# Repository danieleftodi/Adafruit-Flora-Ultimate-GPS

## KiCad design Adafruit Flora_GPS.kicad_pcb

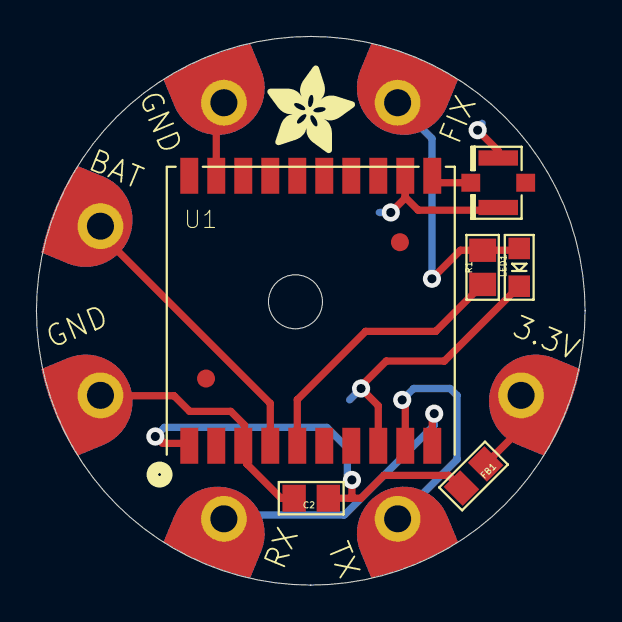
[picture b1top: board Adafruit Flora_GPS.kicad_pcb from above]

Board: 2 copper layers, 30.5 x 30.5 mm, 17 parts (1 on the bottom side), 9 nets.

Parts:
C2: 10uF; 0805
FB1: Ferrite; 0805
FID1, FID2: FIDUCIAL""; FIDUCIAL_1MM
GND0, GND1: SEWTAP-2.0IN; SEWINGTAP_2.0
LED1: FIX; CHIPLED_0805
R1: 1K; 0805
RX0: SEWTAP-2.0IN; SEWINGTAP_2.0
TP1, TP4: SEWTAP-2.0IN; SEWINGTAP_2.0
TX0: SEWTAP-2.0IN; SEWINGTAP_2.0
U1: FGPMMOPA6H
U$6: ADAFRUIT_5MM
U$7: FLORASMALL
U$20: U.FL
UNK3V3IN0: SEWTAP-2.0IN; SEWINGTAP_2.0

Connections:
3.3V: C2.1, FB1.2, U1.P$1
GND: C2.2, GND0.P$1, GND1.P$1, LED1.C, U1.P$3, U1.P$8, U1.P$12, U1.P$19, U$20.P$1, U$20.P$2
unnamed: LED1.A, R1.1, TP4.P$1
unnamed: R1.2, U1.P$5
unnamed: FB1.1, UNK3V3IN0.P$1
unnamed: U1.P$11, U$20.P$3
RX: RX0.P$1, U1.P$10
TX: TX0.P$1, U1.P$9
VBACKUP: TP1.P$1, U1.P$4

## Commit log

2023-01-12 Add: KiCad workspace files
    After import into KiCad, these files where generated.
2023-01-12 Add: Documentation (PDFs)
2023-01-12 Add: Tools
    Use them to control / config the GPS module
